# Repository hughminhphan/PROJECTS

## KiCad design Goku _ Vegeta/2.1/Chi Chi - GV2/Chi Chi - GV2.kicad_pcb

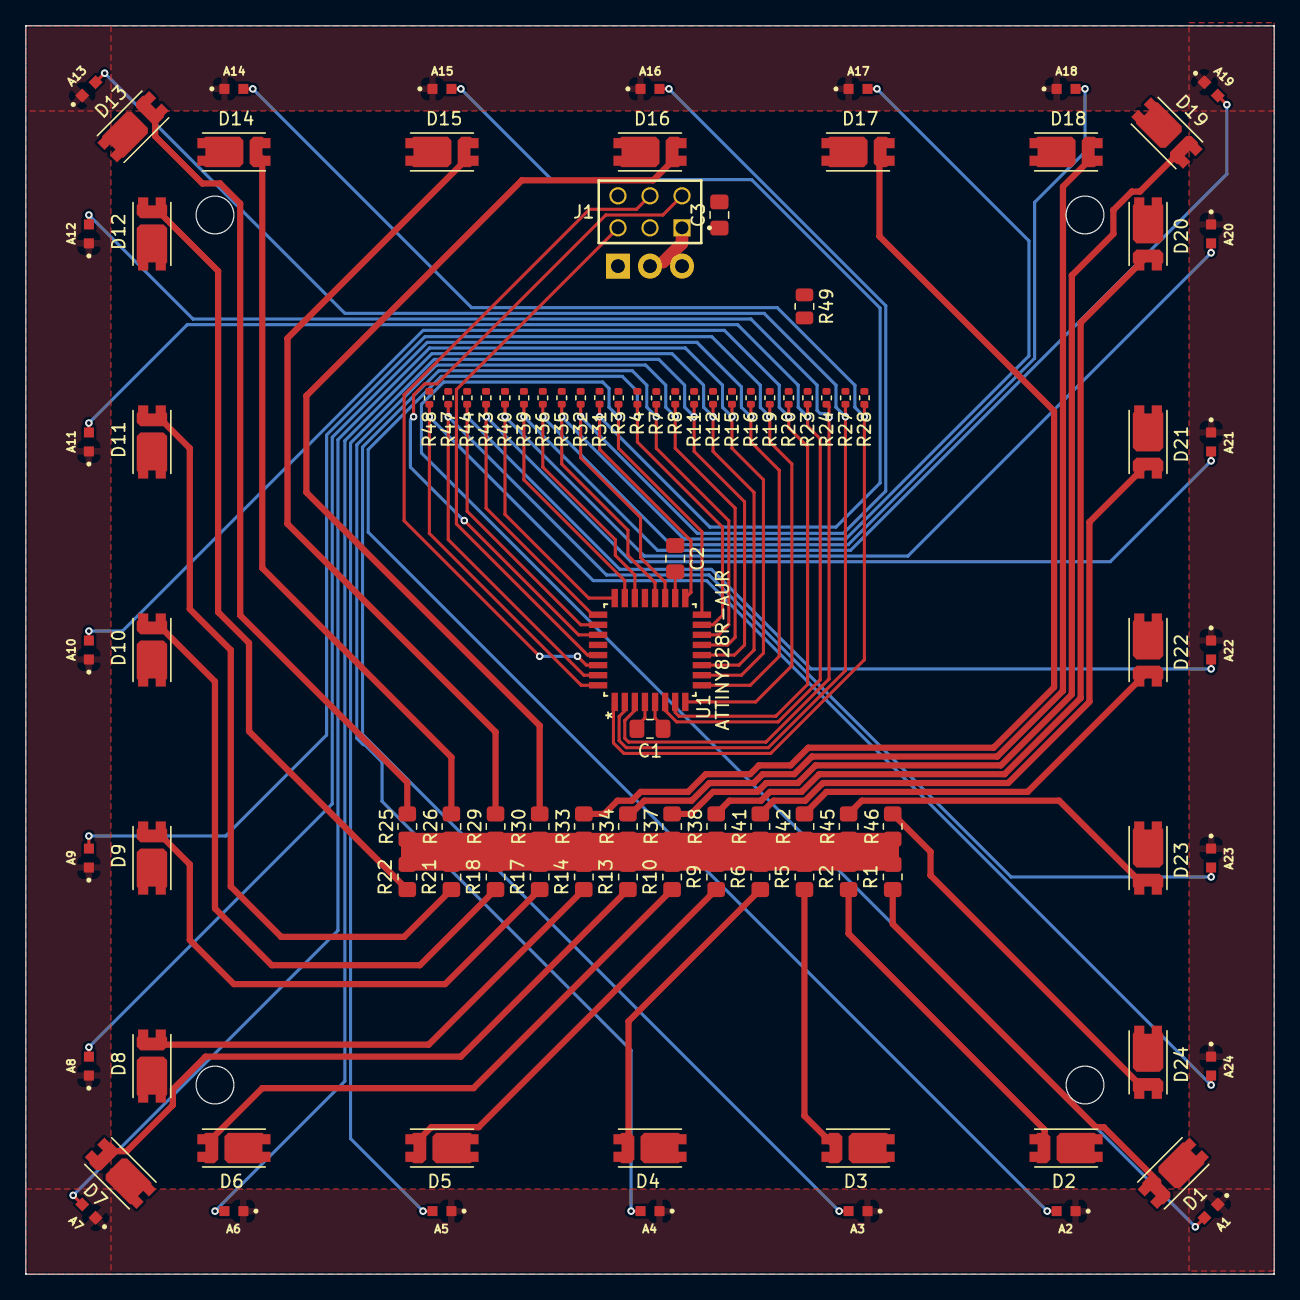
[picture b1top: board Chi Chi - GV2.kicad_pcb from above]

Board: 2 copper layers, 99.0 x 99.0 mm, 103 parts (1 on the bottom side), 55 nets.

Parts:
A1, A2, A3, A4, A5, A6, A7, A8, A9, A10, A11, A12, A13, A14, A15, A16, A17, A18, A19, A20, A21, A22, A23, A24: ALS-PT19-315C/L177/TR8; XDCR_ALS-PT19-315C_L177_TR8
C1, C2: 0.1UF; C_0805_2012Metric_Pad1.18x1.45mm_HandSolder
C3: 10UF; C_0805_2012Metric_Pad1.18x1.45mm_HandSolder
D1, D2, D3, D4, D5, D6, D7, D8, D9, D10, D11, D12, D13, D14, D15, D16, D17, D18, D19, D20, D21, D22, D23, D24: SPMWHT541ML5XATMS6; LED_SPMWHT541MP5WAPKS4
J1: SSQ-103-01-T-D; SAMTEC_SSQ-103-01-T-D
Q1: IRLZ44N; TO-220-3_Vertical
R1, R2, R5, R6, R9, R10, R13, R14, R17, R18, R21, R22, R25, R26, R29, R30, R33, R34, R37, R38, R41, R42, R45, R46: 261R; R_0805_2012Metric_Pad1.20x1.40mm_HandSolder
R3, R4, R7, R8, R11, R12, R15, R16, R19, R20, R23, R24, R27, R28, R31, R32, R35, R36, R39, R40, R43, R44, R47, R48: 10K; R_0402_1005Metric
R49: 10K; R_0805_2012Metric
U1: ATTINY828R-AUR; TQFP32_9X9_MCH

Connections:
+5V: A1.1, A2.1, A3.1, A4.1, A5.1, A6.1, A7.1, A8.1, A9.1, A10.1, A11.1, A12.1, A13.1, A14.1, A15.1, A16.1, A17.1, A18.1, A19.1, A20.1, A21.1, A22.1, A23.1, A24.1, C1.1, C2.1, C3.1, J1.01, R1.1, R2.1, R5.1, R6.1, R9.1, R10.1, R13.1, R14.1, R17.1, R18.1, R21.1, R22.1, R25.1, R26.1, R29.1, R30.1, R33.1, R34.1, R37.1, R38.1, R41.1, R42.1, R45.1, R46.1, U1.4 (VCC), U1.18 (AVCC)
/LEDPWM: J1.06, Q1.1 (G), R49.2
/MSFTDRN: D1.C, D2.C, D3.C, D4.C, D5.C, D6.C, D7.C, D8.C, D9.C, D10.C, D11.C, D12.C, D13.C, D14.C, D15.C, D16.C, D17.C, D18.C, D19.C, D20.C, D21.C, D22.C, D23.C, D24.C, Q1.2 (D)
/RST: J1.05, U1.29 (PD2_(PCINT26/ADC26/RESET/DW))
/SCL: J1.04, U1.30 (PD3_(PCINT27/ADC27/SCL/SCK))
/SDA/MOSI: J1.02, U1.27 (PD0_(PCINT24/ADC24/SDA/MOSI))
/SEN1: A1.2, R3.2, U1.16 ((PCINT7/ADC7)_PA7)
/SEN2: A2.2, R4.2, U1.15 ((PCINT6/ADC6)_PA6)
/SEN3: A3.2, R7.2, U1.14 ((PCINT5/ADC5)_PA5)
/SEN4: A4.2, R8.2, U1.13 ((PCINT4/ADC4)_PA4)
/SEN5: A5.2, R11.2, U1.12 ((PCINT3/ADC3)_PA3)
/SEN6: A6.2, R12.2, U1.11 ((PCINT2/ADC2/AIN1)_PA2)
/SEN7: A7.2, R15.2, U1.10 ((PCINT1/ADC1/AIN0)_PA1)
/SEN8: A8.2, R16.2, U1.9 ((PCINT0/ADC0)_PA0)
/SEN9: A9.2, R19.2, U1.8 ((PCINT23/ADC23/TOCC7/T1)_PC7)
/SEN10: A10.2, R20.2, U1.7 ((PCINT22/ADC22/CLKI/TOCC6)_PC6)
/SEN11: A11.2, R23.2, U1.6 ((PCINT21/ADC21/TOCC5/ICP1/T0)_PC5)
/SEN12: A12.2, R24.2, U1.3 ((PCINT20/ADC20/TOCC4)_PC4)
/SEN13: A13.2, R27.2, U1.2 ((PCINT19/ADC19/TOCC3/TXD)_PC3)
/SEN14: A14.2, R28.2, U1.1 ((PCINT18/ADC18/TOCC2/RXD/INT1)_PC2)
/SEN15: A15.2, R31.2, U1.17 (PB0_(PCINT8/ADC8))
/SEN16: A16.2, R32.2, U1.19 (PB1_(PCINT9/ADC9))
/SEN17: A17.2, R35.2, U1.20 (PB2_(PCINT10/ADC10))
/SEN18: A18.2, R36.2, U1.22 (PB3_(PCINT11/ADC11))
/SEN19: A19.2, R39.2, U1.23 (PB4_(PCINT12/ADC12))
/SEN20: A20.2, R40.2, U1.24 (PB5_(PCINT13/ADC13))
/SEN21: A21.2, R43.2, U1.25 (PB6_(PCINT14/ADC14))
/SEN22: A22.2, R44.2, U1.26 (PB7_(PCINT15/ADC15))
/SEN23: A23.2, R47.2, U1.31 (PC0_(PCINT16/ADC16/TOCC0/SS/XCK))
/SEN24: A24.2, R48.2, U1.32 (PC1_(PCINT17/ADC17/TOCC1/INT0/CLKO))
GND: C1.2, C2.2, C3.2, J1.03, Q1.3 (S), R3.1, R4.1, R7.1, R8.1, R11.1, R12.1, R15.1, R16.1, R19.1, R20.1, R23.1, R24.1, R27.1, R28.1, R31.1, R32.1, R35.1, R36.1, R39.1, R40.1, R43.1, R44.1, R47.1, R48.1, R49.1, U1.5 (GND_2), U1.21 (GND)
unnamed: D1.A, R1.2
unnamed: D2.A, R2.2
unnamed: D3.A, R5.2
unnamed: D4.A, R6.2
unnamed: D5.A, R9.2
unnamed: D6.A, R10.2
unnamed: D7.A, R13.2
unnamed: D8.A, R14.2
unnamed: D9.A, R17.2
unnamed: D10.A, R18.2
unnamed: D11.A, R21.2
unnamed: D12.A, R22.2
unnamed: D13.A, R25.2
unnamed: D14.A, R26.2
unnamed: D15.A, R29.2
unnamed: D16.A, R30.2
unnamed: D17.A, R33.2
unnamed: D18.A, R34.2
unnamed: D19.A, R37.2
unnamed: D20.A, R38.2
unnamed: D21.A, R41.2
unnamed: D22.A, R42.2
unnamed: D23.A, R45.2
unnamed: D24.A, R46.2

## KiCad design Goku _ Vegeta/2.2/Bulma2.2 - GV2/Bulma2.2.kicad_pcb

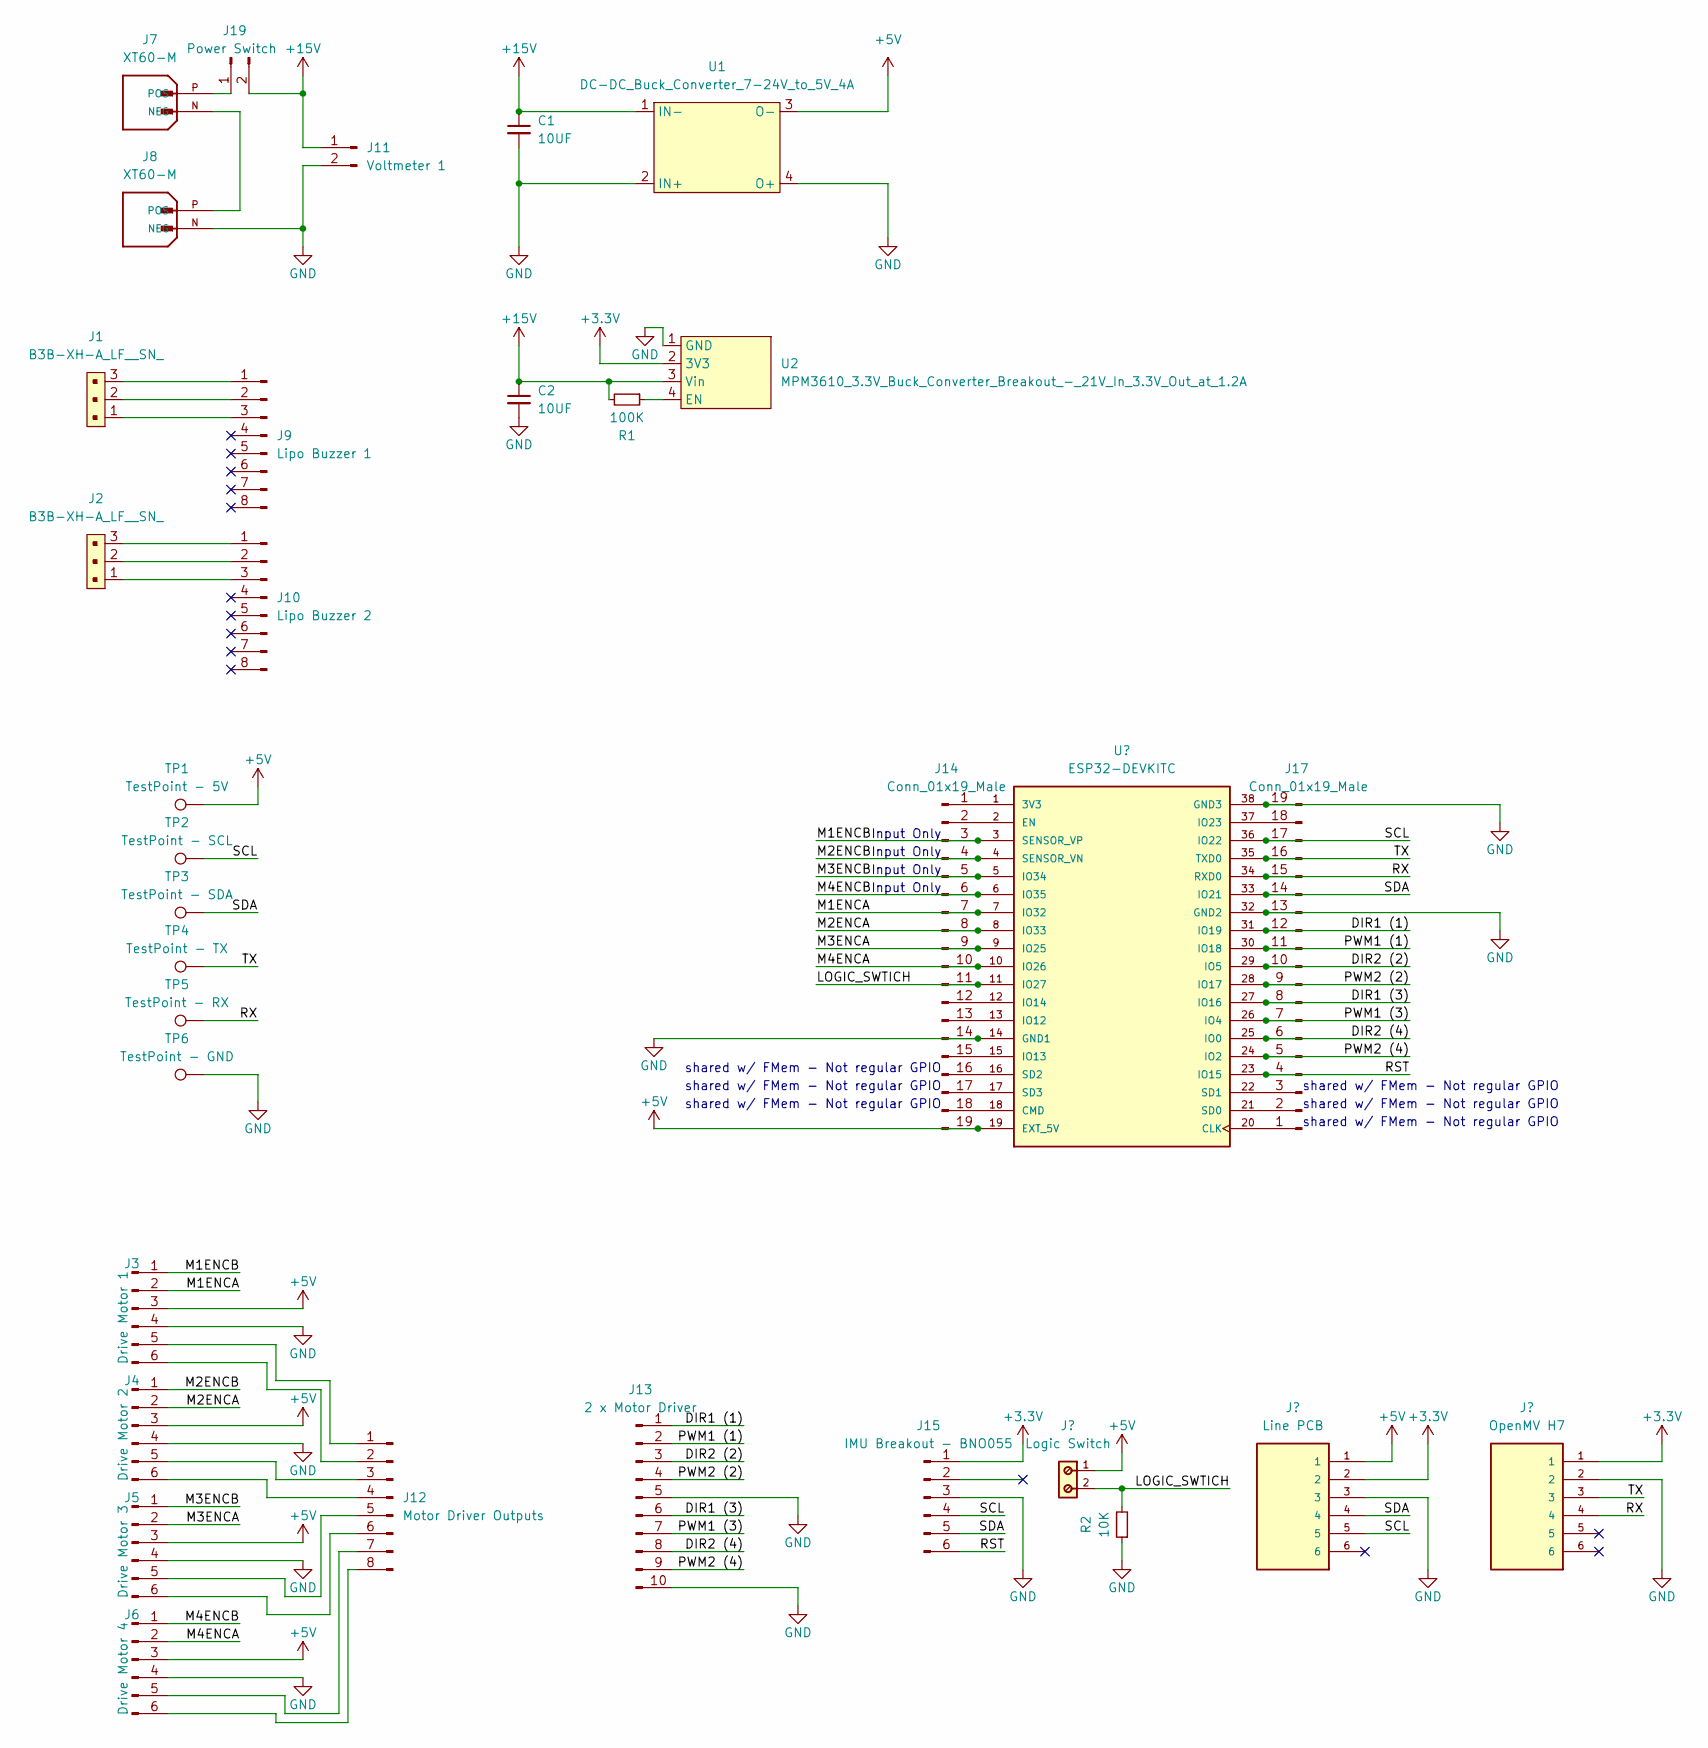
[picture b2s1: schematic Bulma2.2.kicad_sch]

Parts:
C1, C2: 10UF; C_0805_2012Metric
J1, J2: B3B-XH-A_LF__SN_; PinHeader_1x3_P2.5mm_Drill1.1mm; MPN B3B-XH-A(LF)(SN); Digi-Key_PN 455-2248-ND
J3: Drive Motor 1; PinSocket_1x06_P2.54mm_Vertical
J4: Drive Motor 2; PinHeader_1x06_P2.54mm_Vertical
J5: Drive Motor 3; PinSocket_1x06_P2.54mm_Vertical
J6: Drive Motor 4; PinSocket_1x06_P2.54mm_Vertical
J7, J8: XT60-M; AMASS_XT60-M; PARTREV V1.2
J9: Lipo Buzzer 1; Lipo Buzzer Vertical
J10: Lipo Buzzer 2; Lipo Buzzer Vertical
J11: Voltmeter 1; PinHeader_1x02_P2.54mm_Vertical
J12: Motor Driver Outputs; PinHeader_1x08_P2.54mm_Vertical
J13: 2 x Motor Driver; PinHeader_1x10_P2.54mm_Vertical
J14, J17: Conn_01x19_Male; PinHeader_1x19_P2.54mm_Vertical
J15: IMU Breakout - BNO055; Adafruit IMU BNO055
J19: Power Switch; PinHeader_1x02_P2.54mm_Vertical
R1: 100K; R_0805_2012Metric
R2: 10K; R_0805_2012Metric
TP1: TestPoint - 5V; TestPoint_THTPad_D2.0mm_Drill1.0mm
TP2: TestPoint - SCL; TestPoint_THTPad_D2.0mm_Drill1.0mm
TP3: TestPoint - SDA; TestPoint_THTPad_D2.0mm_Drill1.0mm
TP4: TestPoint - TX; TestPoint_THTPad_D2.0mm_Drill1.0mm
TP5: TestPoint - RX; TestPoint_THTPad_D2.0mm_Drill1.0mm
TP6: TestPoint - GND; TestPoint_THTPad_D2.0mm_Drill1.0mm
U1: DC-DC_Buck_Converter_7-24V_to_5V_4A
U2: MPM3610_3.3V_Buck_Converter_Breakout_-_21V_In_3.3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; MPM3610 3.3V Buck Converter Breakout - 21V In 3.3V Out at 1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

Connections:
+3.3V: J15.1, U2.2 (3V3); also elsewhere on the board
+5V: J3.3, J4.3, J5.3, J6.3, J14.19, TP1.1, U1.3 (O-); also elsewhere on the board
+15V: C1.1, C2.1, J11.1, J19.2, R1.2, U1.1 (IN-), U2.3 (Vin)
/DIR1 (1): J13.1, J17.12; also elsewhere on the board
/DIR1 (3): J13.6, J17.8; also elsewhere on the board
/DIR2 (2): J13.3, J17.10; also elsewhere on the board
/DIR2 (4): J13.8, J17.6; also elsewhere on the board
/LOGIC_SWTICH: J14.11, R2.2; also elsewhere on the board
/M1ENCA: J3.2, J14.7; also elsewhere on the board
/M1ENCB: J3.1, J14.3; also elsewhere on the board
/M2ENCA: J4.2, J14.8; also elsewhere on the board
/M2ENCB: J4.1, J14.4; also elsewhere on the board
/M3ENCA: J5.2, J14.9; also elsewhere on the board
/M3ENCB: J5.1, J14.5; also elsewhere on the board
/M4ENCA: J6.2, J14.10; also elsewhere on the board
/M4ENCB: J6.1, J14.6; also elsewhere on the board
/PWM1 (1): J13.2, J17.11; also elsewhere on the board
/PWM1 (3): J13.7, J17.7; also elsewhere on the board
/PWM2 (2): J13.4, J17.9; also elsewhere on the board
/PWM2 (4): J13.9, J17.5; also elsewhere on the board
/RST: J15.6, J17.4; also elsewhere on the board
/RX: J17.15, TP5.1; also elsewhere on the board
/SCL: J15.4, J17.17, TP2.1; also elsewhere on the board
/SDA: J15.5, J17.14, TP3.1; also elsewhere on the board
/TX: J17.16, TP4.1; also elsewhere on the board
GND: C1.2, C2.2, J3.4, J4.4, J5.4, J6.4, J8.N (NEG), J11.2, J13.5, J13.10, J14.14, J15.3, J17.13, J17.19, R2.1, TP6.1, U1.2 (IN+), U1.4 (O+), U2.1 (GND); also elsewhere on the board
unnamed: J7.N (NEG), J8.P (POS)
unnamed: J1.3, J9.1
unnamed: J1.2, J9.2
unnamed: J1.1, J9.3
unnamed: J2.3, J10.1
unnamed: J2.2, J10.2
unnamed: J2.1, J10.3
unnamed: J3.5, J12.1
unnamed: J3.6, J12.2
unnamed: J4.5, J12.3
unnamed: J4.6, J12.4
unnamed: J5.5, J12.5
unnamed: J5.6, J12.6
unnamed: J6.5, J12.7
unnamed: J6.6, J12.8
unnamed 41: J14.1; also elsewhere on the board
unnamed 42: J14.2; also elsewhere on the board
unnamed 43: J14.12; also elsewhere on the board
unnamed 44: J14.13; also elsewhere on the board
unnamed 45: J14.15; also elsewhere on the board
unnamed 46: J14.16; also elsewhere on the board
unnamed 47: J14.17; also elsewhere on the board
unnamed 48: J14.18; also elsewhere on the board
unnamed 49: J17.1; also elsewhere on the board
unnamed 50: J17.2; also elsewhere on the board
unnamed 51: J17.3; also elsewhere on the board
unnamed 52: J17.18; also elsewhere on the board
unnamed: J7.P (POS), J19.1
unnamed: R1.1, U2.4 (EN)

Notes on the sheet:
Input Only
shared w/ FMem - Not regular GPIO

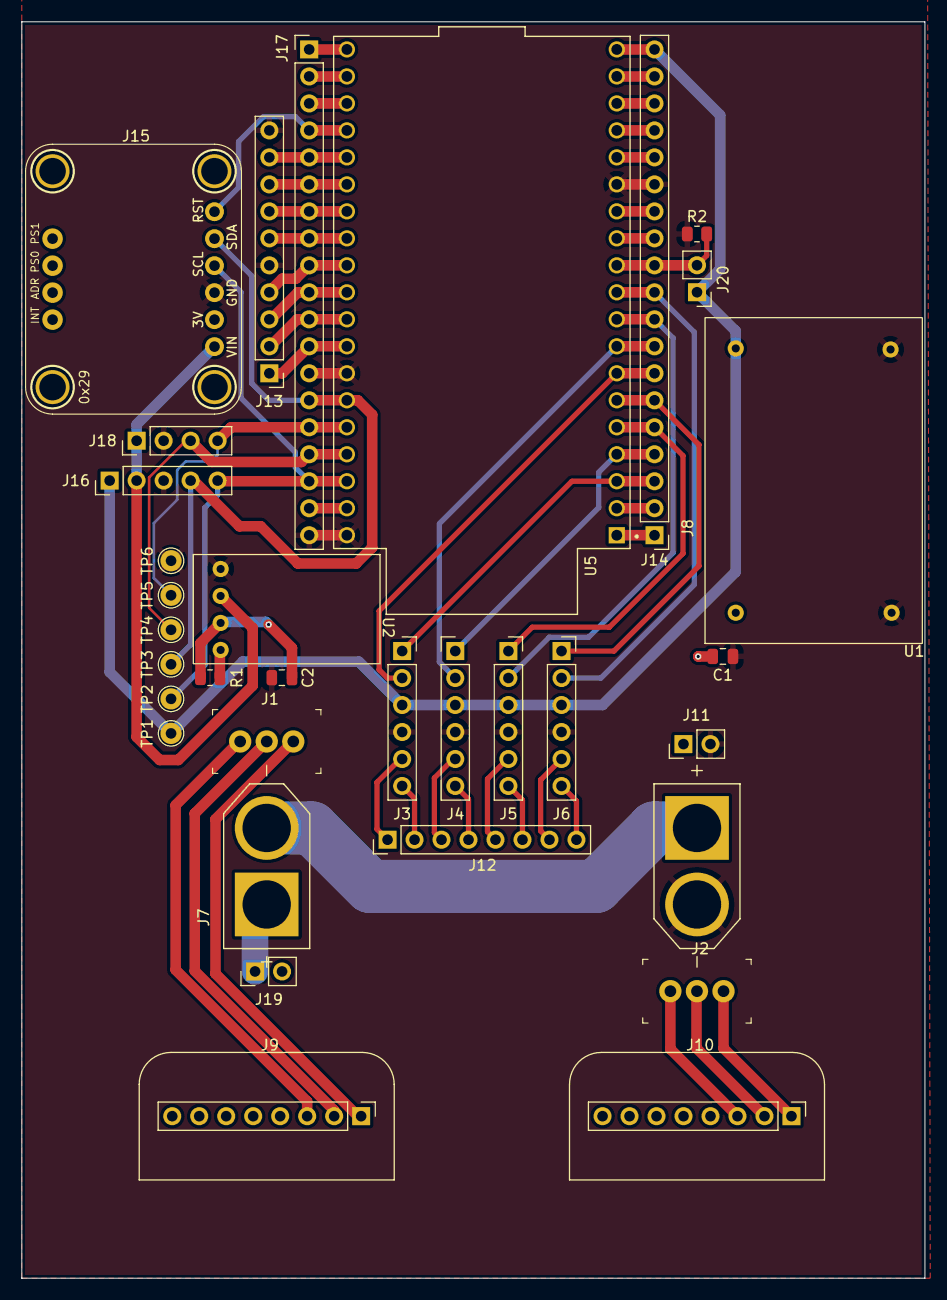
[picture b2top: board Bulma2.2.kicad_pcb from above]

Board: 2 copper layers, 85.0 x 118.2 mm, 33 parts (0 on the bottom side), 55 nets.

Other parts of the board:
J16: Line PCB; PinHeader_1x05_P2.54mm_Vertical
J18: H7; PinHeader_1x04_P2.54mm_Vertical
J20: Logic Switch; PinHeader_1x02_P2.54mm_Vertical
U5: ESP32-DEVKITC; MODULE_ESP32-DEVKITC

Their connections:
+3.3V: J16.2, J18.1; also elsewhere on the board
+5V: J16.1, J20.1, U5.19 (EXT_5V); also elsewhere on the board
/DIR1 (1): U5.31 (IO19); also elsewhere on the board
/DIR1 (3): U5.27 (IO16); also elsewhere on the board
/DIR2 (2): U5.29 (IO5); also elsewhere on the board
/DIR2 (4): U5.25 (IO0); also elsewhere on the board
/LOGIC_SWTICH: J20.2, U5.11 (IO27); also elsewhere on the board
/M1ENCA: U5.7 (IO32); also elsewhere on the board
/M1ENCB: U5.3 (SENSOR_VP); also elsewhere on the board
/M2ENCA: U5.8 (IO33); also elsewhere on the board
/M2ENCB: U5.4 (SENSOR_VN); also elsewhere on the board
/M3ENCA: U5.9 (IO25); also elsewhere on the board
/M3ENCB: U5.5 (IO34); also elsewhere on the board
/M4ENCA: U5.10 (IO26); also elsewhere on the board
/M4ENCB: U5.6 (IO35); also elsewhere on the board
/PWM1 (1): U5.30 (IO18); also elsewhere on the board
/PWM1 (3): U5.26 (IO4); also elsewhere on the board
/PWM2 (2): U5.28 (IO17); also elsewhere on the board
/PWM2 (4): U5.24 (IO2); also elsewhere on the board
/RST: U5.23 (IO15); also elsewhere on the board
/RX: J18.4, U5.34 (RXD0); also elsewhere on the board
/SCL: J16.5, U5.36 (IO22); also elsewhere on the board
/SDA: J16.4, U5.33 (IO21); also elsewhere on the board
/TX: J18.3, U5.35 (TXD0); also elsewhere on the board
GND: J16.3, J18.2, U5.14 (GND1), U5.32 (GND2), U5.38 (GND3); also elsewhere on the board
unnamed 41: U5.1 (3V3); also elsewhere on the board
unnamed 42: U5.2 (EN); also elsewhere on the board
unnamed 43: U5.12 (IO14); also elsewhere on the board
unnamed 44: U5.13 (IO12); also elsewhere on the board
unnamed 45: U5.15 (IO13); also elsewhere on the board
unnamed 46: U5.16 (SD2); also elsewhere on the board
unnamed 47: U5.17 (SD3); also elsewhere on the board
unnamed 48: U5.18 (CMD); also elsewhere on the board
unnamed 49: U5.20 (CLK); also elsewhere on the board
unnamed 50: U5.21 (SD0); also elsewhere on the board
unnamed 51: U5.22 (SD1); also elsewhere on the board
unnamed 52: U5.37 (IO23); also elsewhere on the board

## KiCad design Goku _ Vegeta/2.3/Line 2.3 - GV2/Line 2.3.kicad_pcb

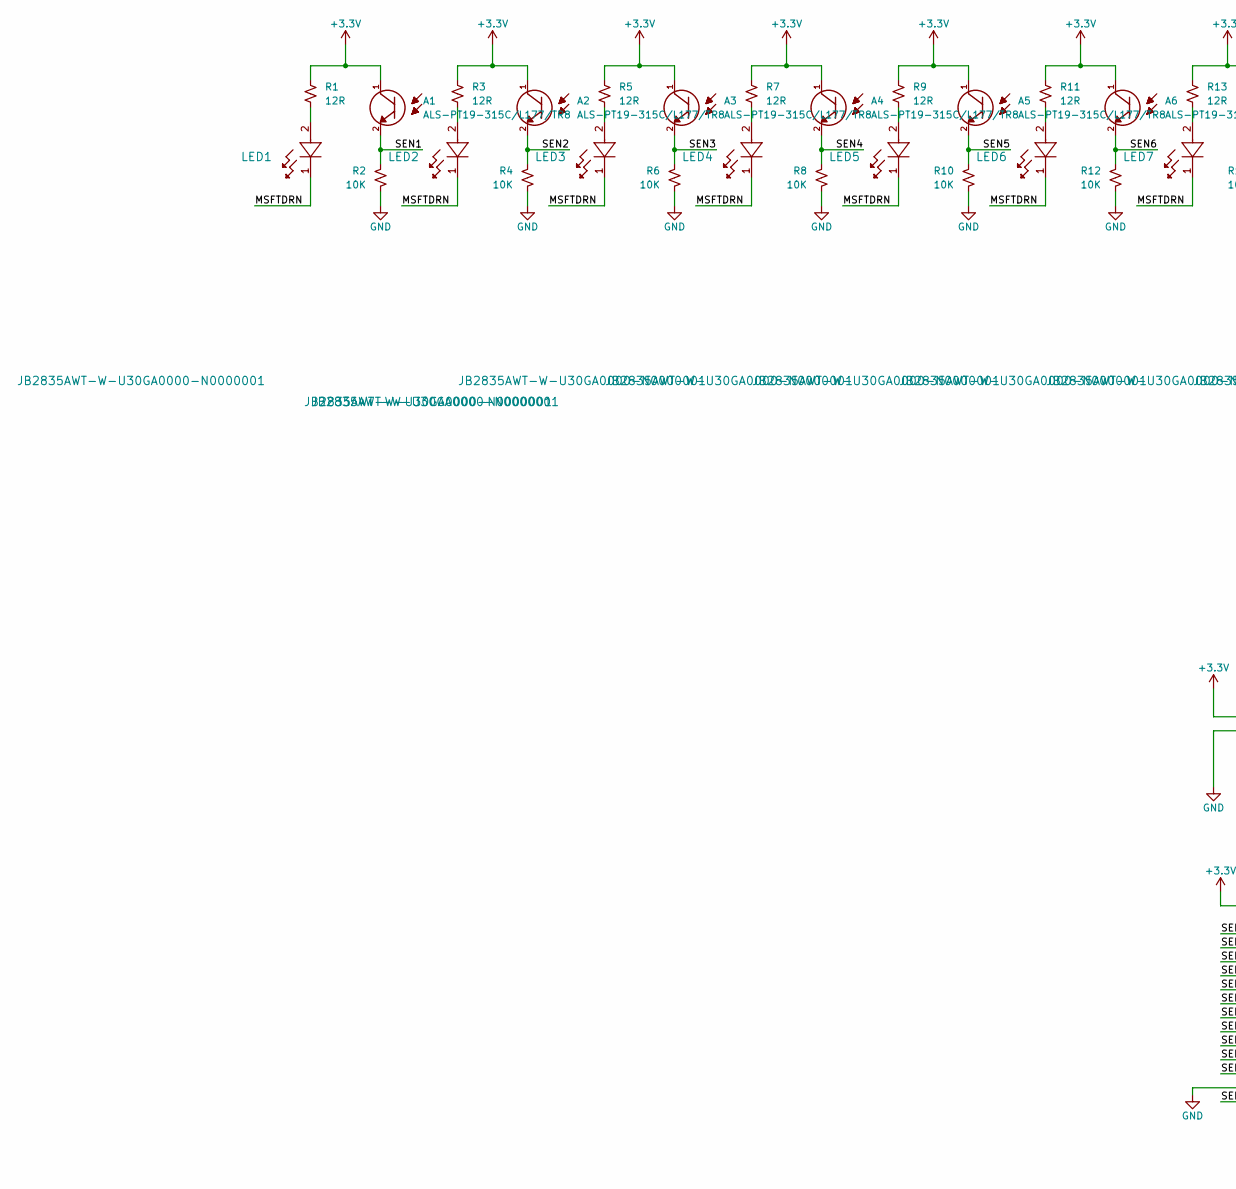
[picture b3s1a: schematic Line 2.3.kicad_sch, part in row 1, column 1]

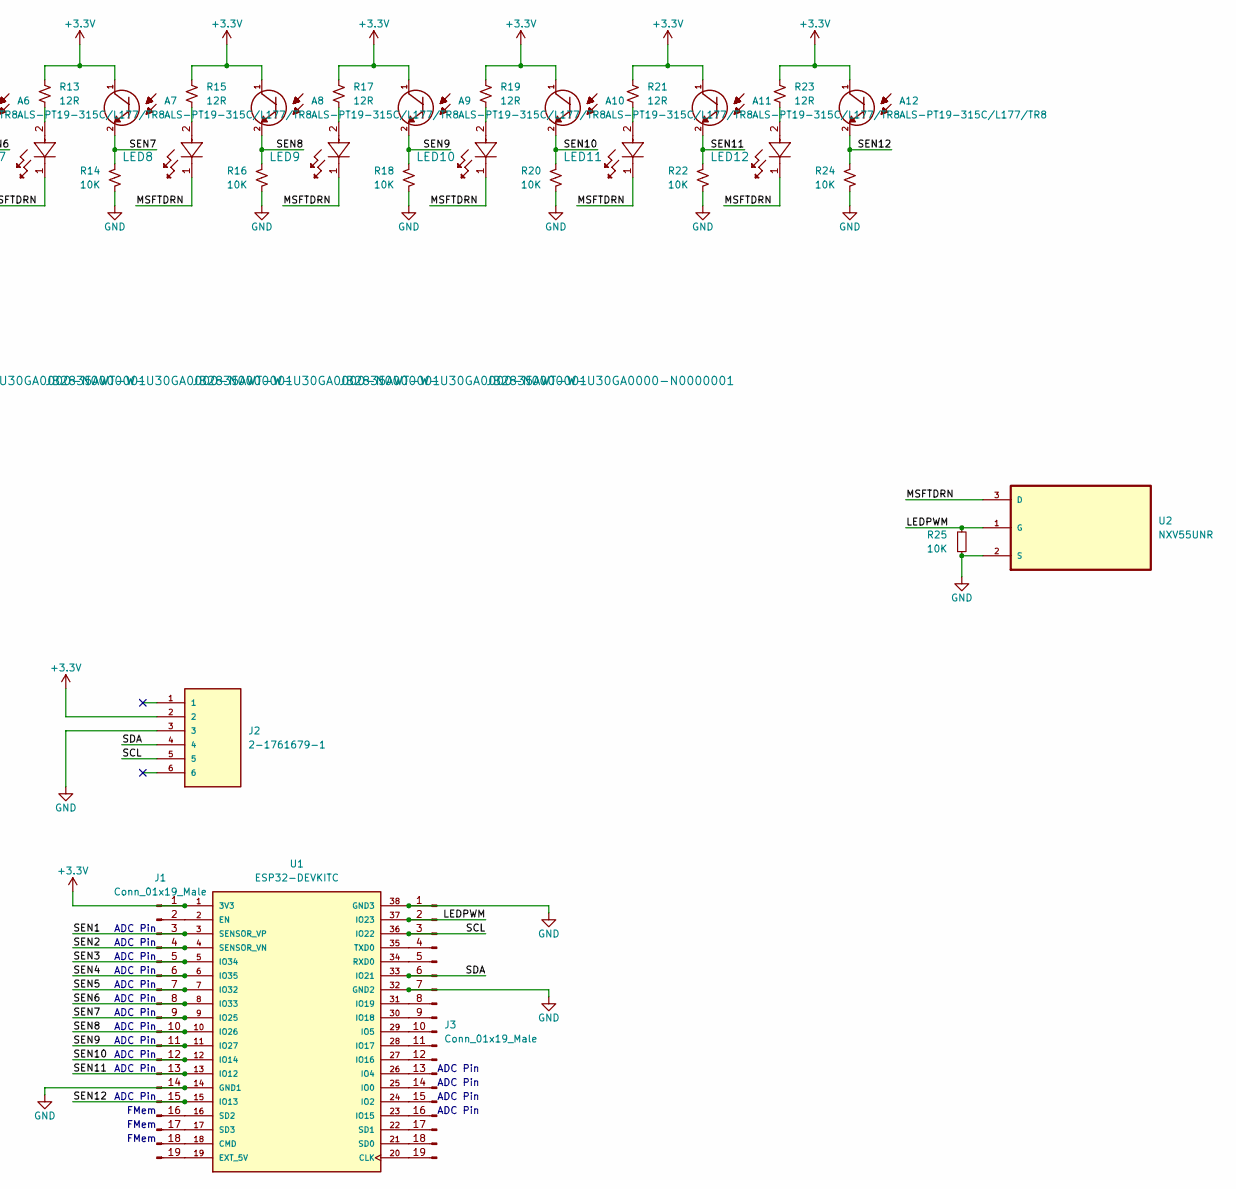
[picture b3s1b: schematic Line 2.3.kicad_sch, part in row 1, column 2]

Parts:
A1, A2, A3, A4, A5, A6, A7, A8, A9, A10, A11, A12: ALS-PT19-315C/L177/TR8; XDCR_ALS-PT19-315C/L177/TR8; PARTREV 5
J1, J3: Conn_01x19_Male; PinHeader_1x19_P2.54mm_Vertical
J2: 2-1761679-1; Box IDC header 2x3
LED1, LED2, LED3, LED4, LED5, LED6, LED7, LED8, LED9, LED10, LED11, LED12: JB2835AWT-W-U30GA0000-N0000001; LED_J2835_CRW
R1, R3, R5, R7, R9, R11, R13, R15, R17, R19, R21, R23: 12R; R_0805_2012Metric
R2, R4, R6, R8, R10, R12, R14, R16, R18, R20, R22, R24, R25: 10K; R_0805_2012Metric
U1: ESP32-DEVKITC; MODULE_ESP32-DEVKITC; PARTREV N/A
U2: NXV55UNR; TRANS_BC846B,215

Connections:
/LEDPWM: J3.2, R25.2, U1.37 (IO23), U2.1 (G)
/MSFTDRN: LED1.1, LED2.1, LED3.1, LED4.1, LED5.1, LED6.1, LED7.1, LED8.1, LED9.1, LED10.1, LED11.1, LED12.1, U2.3 (D)
/SCL: J2.5, J3.3, U1.36 (IO22)
/SDA: J2.4, J3.6, U1.33 (IO21)
/SEN1: A1.2, J1.3, R2.2, U1.3 (SENSOR_VP)
/SEN2: A2.2, J1.4, R4.2, U1.4 (SENSOR_VN)
/SEN3: A3.2, J1.5, R6.2, U1.5 (IO34)
/SEN4: A4.2, J1.6, R8.2, U1.6 (IO35)
/SEN5: A5.2, J1.7, R10.2, U1.7 (IO32)
/SEN6: A6.2, J1.8, R12.2, U1.8 (IO33)
/SEN7: A7.2, J1.9, R14.2, U1.9 (IO25)
/SEN8: A8.2, J1.10, R16.2, U1.10 (IO26)
/SEN9: A9.2, J1.11, R18.2, U1.11 (IO27)
/SEN10: A10.2, J1.12, R20.2, U1.12 (IO14)
/SEN11: A11.2, J1.13, R22.2, U1.13 (IO12)
/SEN12: A12.2, J1.15, R24.2, U1.15 (IO13)
GND: J1.14, J2.3, J3.1, J3.7, R2.1, R4.1, R6.1, R8.1, R10.1, R12.1, R14.1, R16.1, R18.1, R20.1, R22.1, R24.1, R25.1, U1.14 (GND1), U1.32 (GND2), U1.38 (GND3), U2.2 (S)
unnamed: J1.2, U1.2 (EN)
unnamed: J1.16, U1.16 (SD2)
unnamed: J1.17, U1.17 (SD3)
unnamed: J1.18, U1.18 (CMD)
unnamed: J1.19, U1.19 (EXT_5V)
unnamed: J3.4, U1.35 (TXD0)
unnamed: J3.5, U1.34 (RXD0)
unnamed: J3.8, U1.31 (IO19)
unnamed: J3.9, U1.30 (IO18)
unnamed: J3.10, U1.29 (IO5)
unnamed: J3.11, U1.28 (IO17)
unnamed: J3.12, U1.27 (IO16)
unnamed: J3.13, U1.26 (IO4)
unnamed: J3.14, U1.25 (IO0)
unnamed: J3.15, U1.24 (IO2)
unnamed: J3.16, U1.23 (IO15)
unnamed: J3.17, U1.22 (SD1)
unnamed: J3.18, U1.21 (SD0)
unnamed: J3.19, U1.20 (CLK)
unnamed: LED1.2, R1.2
unnamed: LED2.2, R3.2
unnamed: LED3.2, R5.2
unnamed: LED4.2, R7.2
unnamed: LED5.2, R9.2
unnamed: LED6.2, R11.2
unnamed: LED7.2, R13.2
unnamed: LED8.2, R15.2
unnamed: LED9.2, R17.2
unnamed: LED10.2, R19.2
unnamed: LED11.2, R21.2
unnamed: LED12.2, R23.2

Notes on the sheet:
ADC Pin
FMem

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
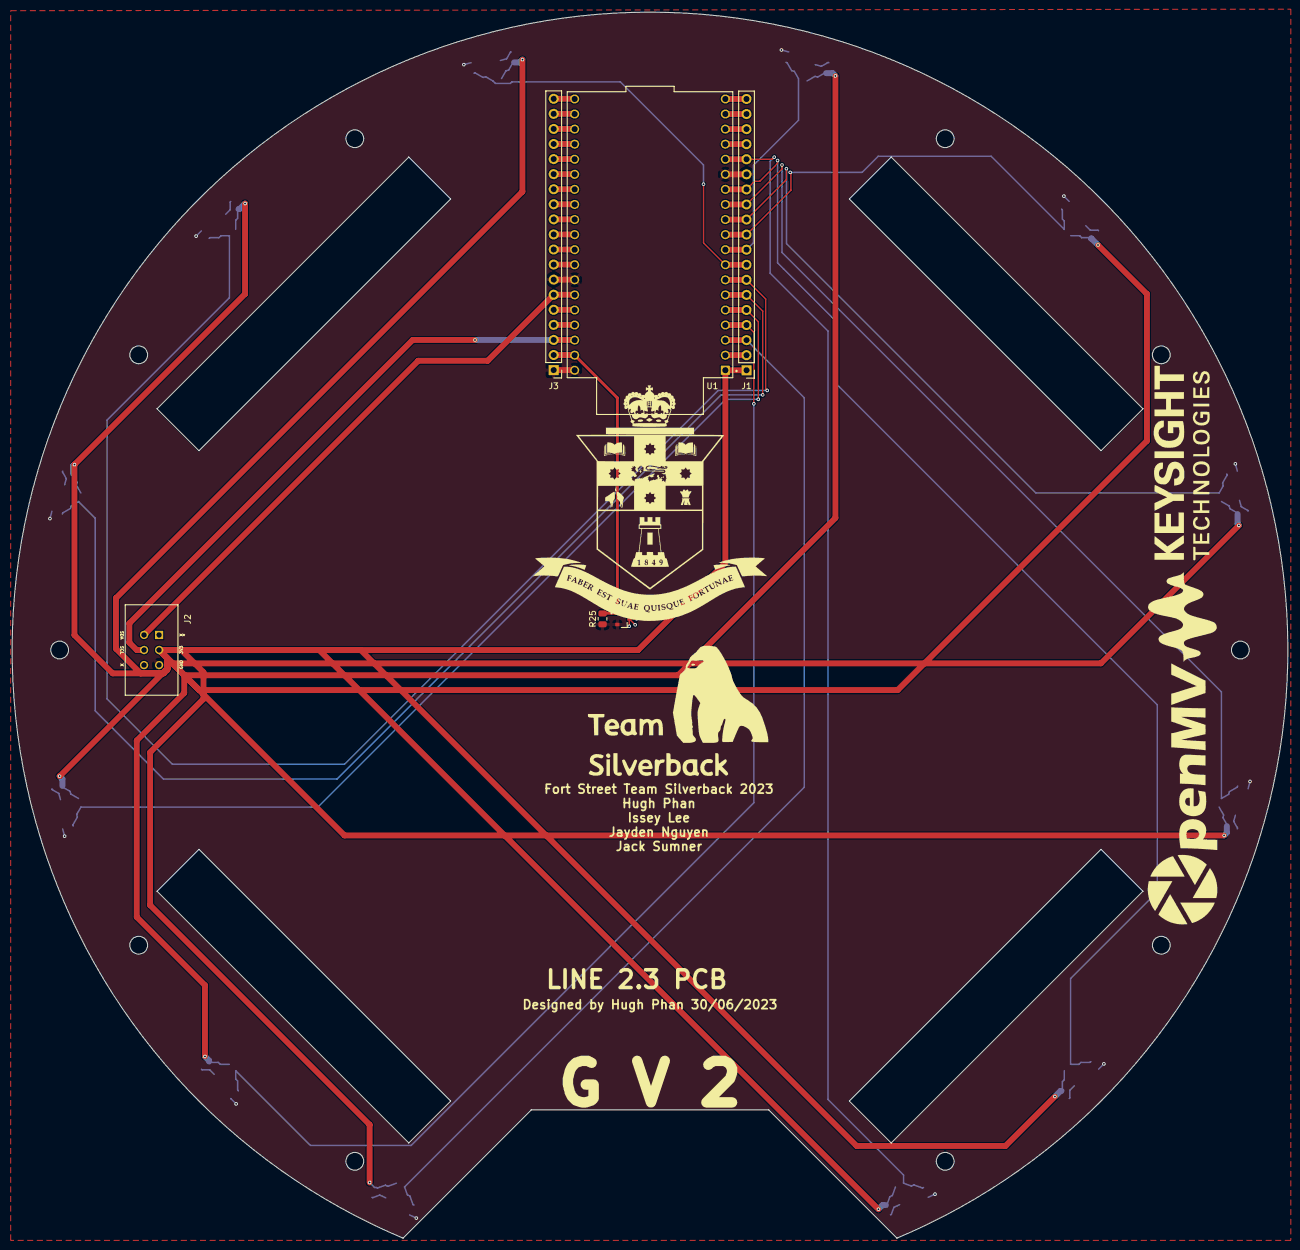
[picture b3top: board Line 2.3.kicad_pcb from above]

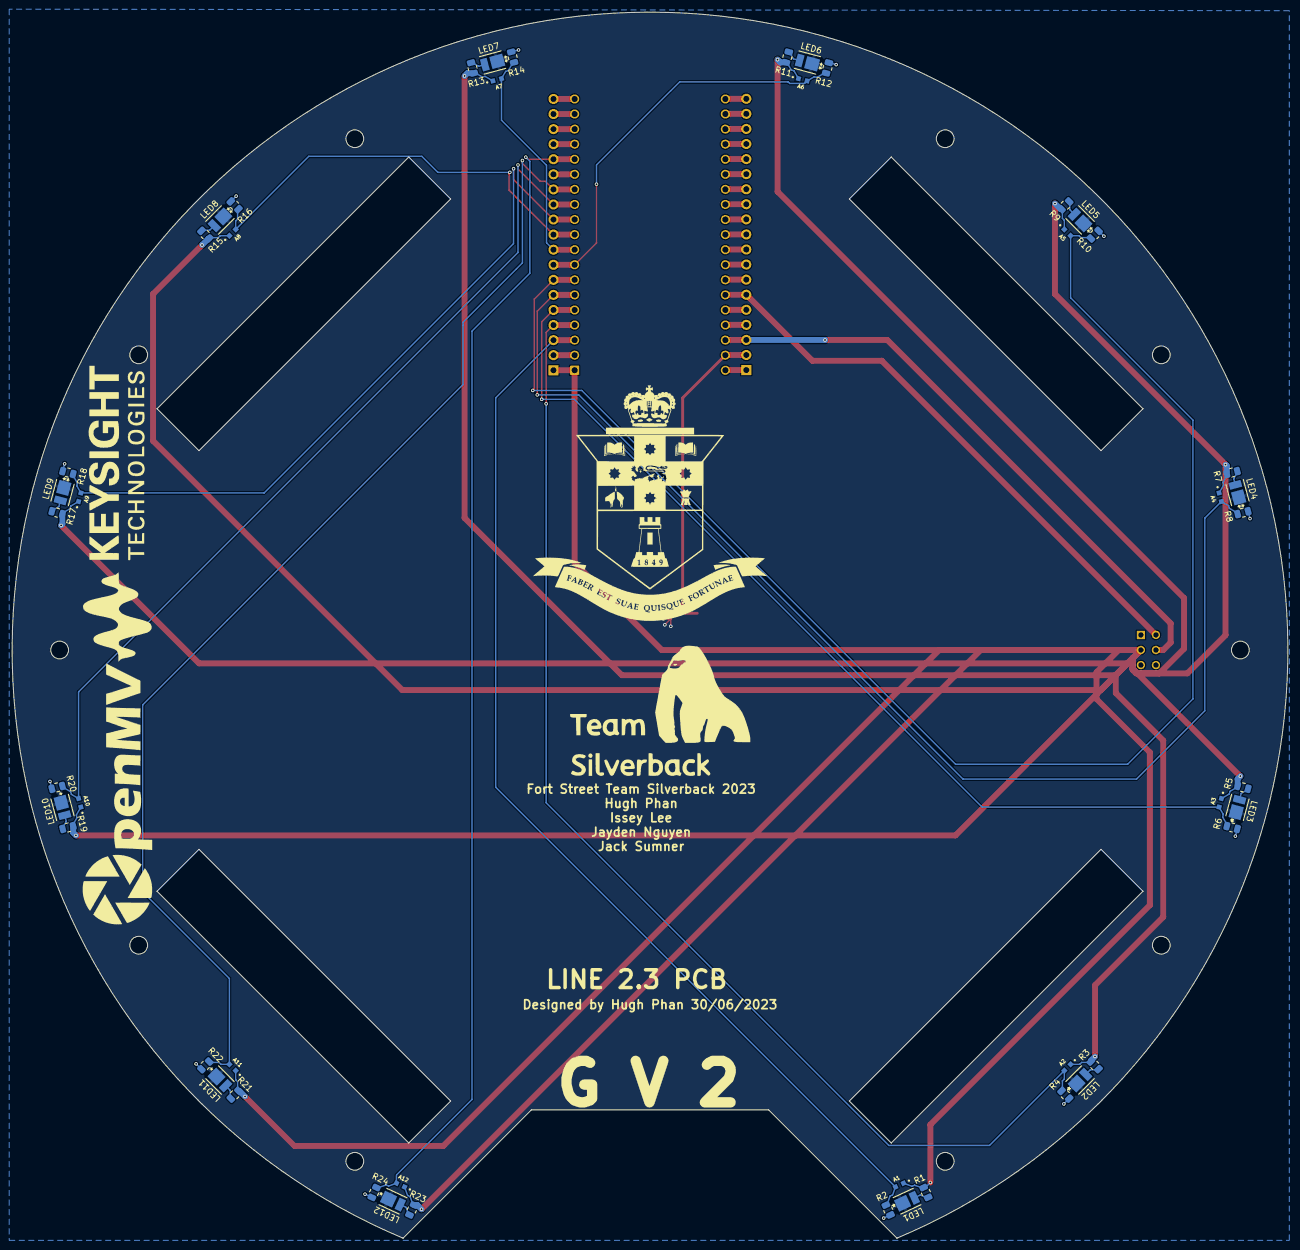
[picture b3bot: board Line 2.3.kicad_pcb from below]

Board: 2 copper layers, 215.0 x 206.6 mm, 54 parts (48 on the bottom side), 49 nets.

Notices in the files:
parts and their libraries:
COPYRIGHT: Copyright (C) 2018 Accelerated Designs. All rights reserved
